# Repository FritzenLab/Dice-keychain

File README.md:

# Dice-keychain
 More info at https://fritzenlab.net/electronic-dice-in-keychain-format/

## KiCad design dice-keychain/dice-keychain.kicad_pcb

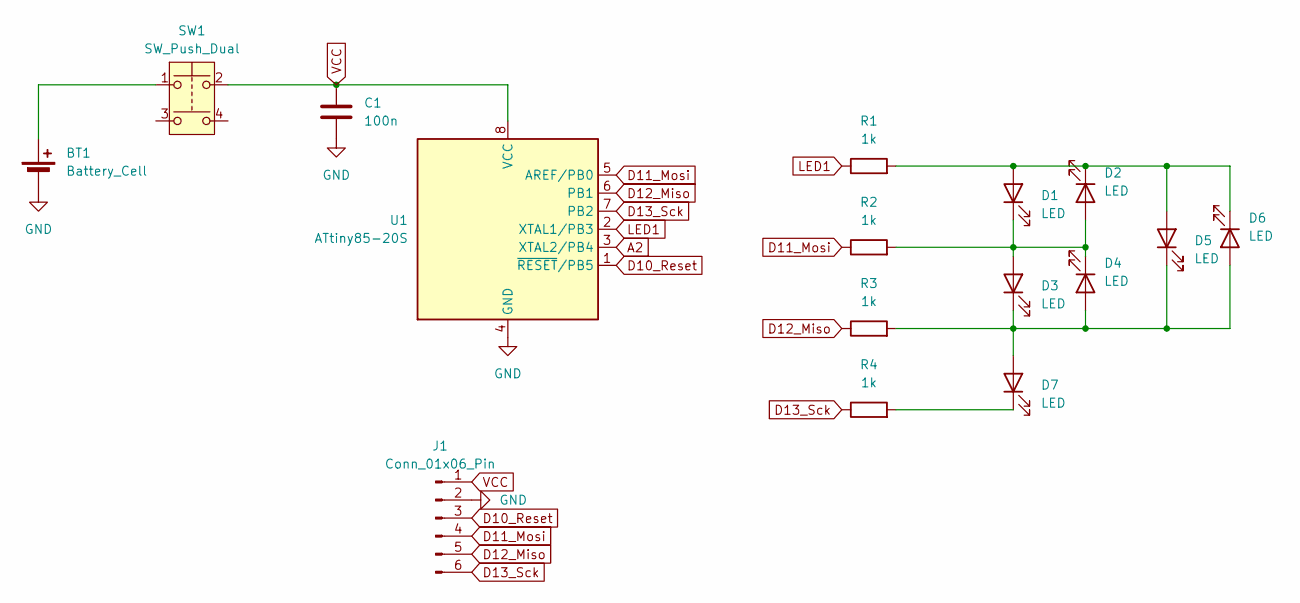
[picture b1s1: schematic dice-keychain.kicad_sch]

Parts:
BT1: Battery_Cell; BatteryHolder_Multicomp_BC-2001_1x2032
C1: 100n; C_0805_2012Metric
D1, D2, D3, D4, D5, D6, D7: LED; LED_0805_2012Metric
J1: Conn_01x06_Pin; PinHeader_1x06_P2.54mm_Vertical
R1, R2, R3, R4: 1k; R_0805_2012Metric
SW1: SW_Push_Dual; SW_Push_1P1T_NO_6x6mm_H9.5mm
U1: ATtiny85-20S; SOIC-8W_5.3x5.3mm_P1.27mm

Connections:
A2: U1.3 (XTAL2/PB4)
D10_Reset: J1.3, U1.1 (~RESET/PB5)
D11_Mosi: J1.4, R2.1, U1.5 (AREF/PB0)
D12_Miso: J1.5, R3.1, U1.6 (PB1)
D13_Sck: J1.6, R4.1, U1.7 (PB2)
GND: BT1.2 (-), C1.2, J1.2, U1.4 (GND)
LED1: R1.1, U1.2 (XTAL1/PB3)
unnamed: BT1.1 (+), SW1.1
unnamed: D1.2 (A), D2.1 (K), D5.2 (A), D6.1 (K), R1.2
unnamed: D1.1 (K), D2.2 (A), D3.2 (A), D4.1 (K), R2.2
unnamed: D3.1 (K), D4.2 (A), D5.1 (K), D6.2 (A), D7.2 (A), R3.2
unnamed: D7.1 (K), R4.2
VCC: C1.1, J1.1, SW1.2, U1.8 (VCC)

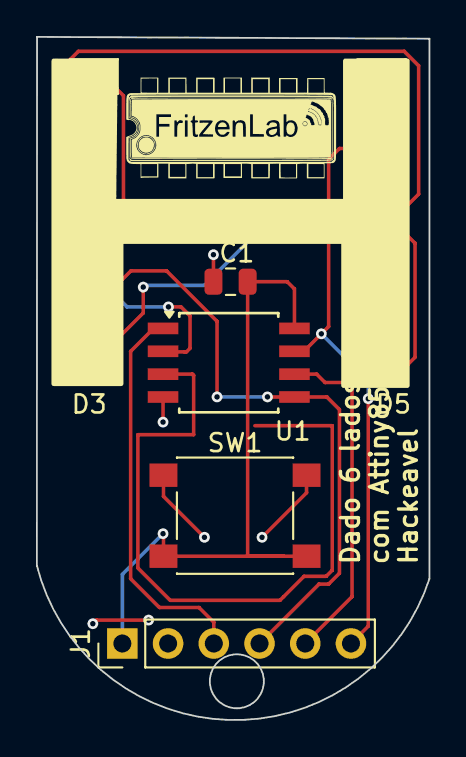
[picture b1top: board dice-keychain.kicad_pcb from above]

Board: 2 copper layers, 21.8 x 37.9 mm, 16 parts (1 on the bottom side), 12 nets.

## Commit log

2024-11-07 created schematics
2024-11-07 backups
2024-11-07 finished PCB, generated Gerber
2024-11-07 PCB modified, added top silkscreen on LEDs
2024-11-08 added images (prints)
2024-12-19 added test code
2024-12-21 implemented (mostly) correct code
2025-01-14 finished coding
2025-01-14 Update README.md
    added readme
2025-01-14 Update README.md
    corrected typo
2025-01-14 added images, finished code
2025-02-09 edited code
2025-02-09 finished code
2025-02-09 housekeeping
